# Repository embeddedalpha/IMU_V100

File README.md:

# Innertial Measurement System

## Version: 1.0.0

## Project Structure

```

    📁 Case
    📁 Firmware
    📁 Marketing and Documentation
    📁 Media
    📁 PCB
    📁 Software
    📁 Simulations
    📁 Wires and Cables
    📄 README.md

```

## Architecture

### [Architecture's PDF](PCB/PDFs/IMU_V100.pdf)

### [EW0201DW](Drawings/EW0201DW.pdf)

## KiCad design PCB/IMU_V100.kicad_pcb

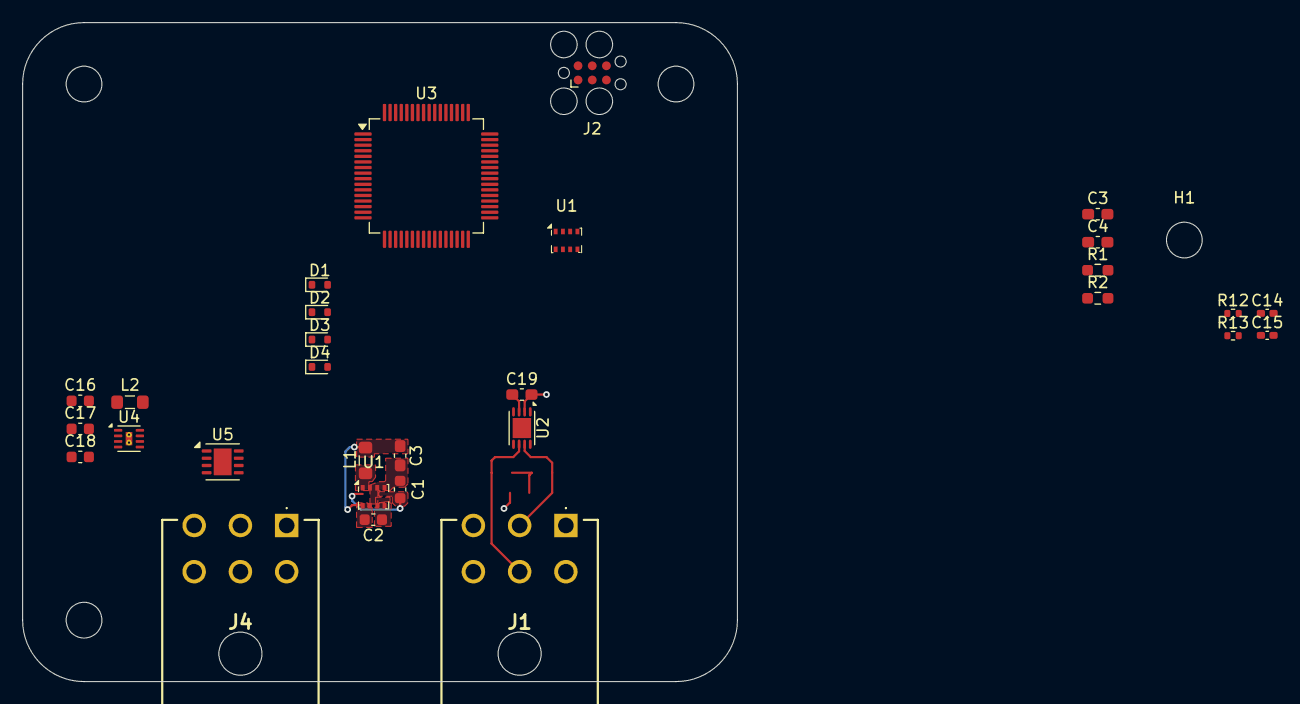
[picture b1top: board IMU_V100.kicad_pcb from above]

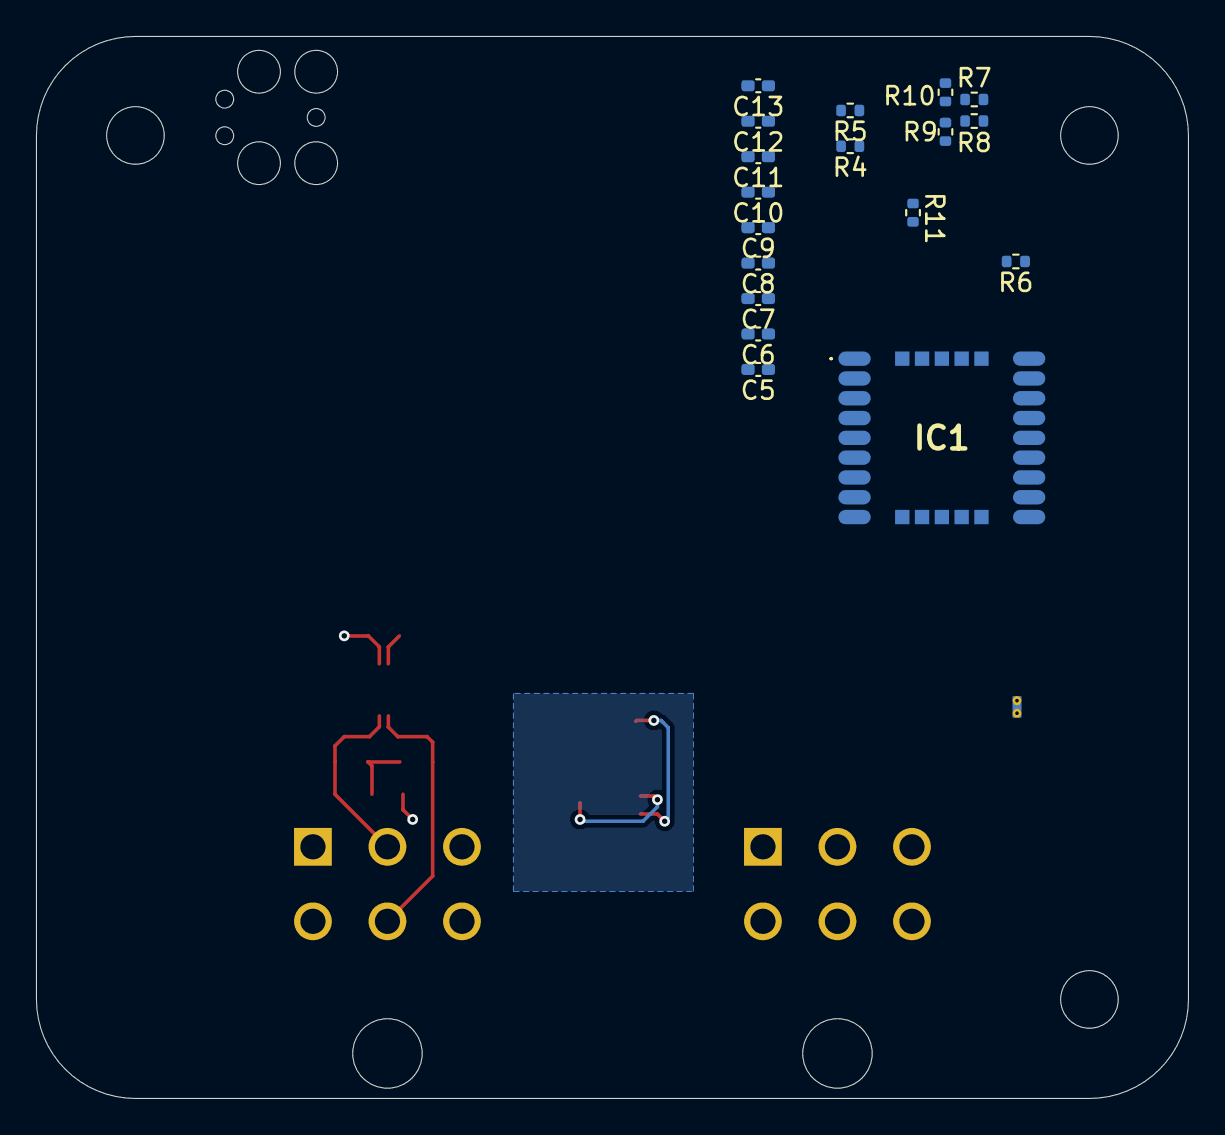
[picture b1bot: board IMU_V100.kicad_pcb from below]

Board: 2 copper layers, 64.0 x 59.0 mm, 52 parts (18 on the bottom side), 25 nets.

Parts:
C1, C16, C18: 4.7uF; C_0603_1608Metric
C2, C17: 560nF; C_0603_1608Metric
C3, C3#2, C19: 0.1uF; C_0603_1608Metric_Pad1.08x0.95mm_HandSolder
C4: 4700pF; C_0603_1608Metric_Pad1.08x0.95mm_HandSolder
C5, C7, C10: 10uF; C_0402_1005Metric_Pad0.74x0.62mm_HandSolder
C6, C8, C13: 100nF; C_0402_1005Metric_Pad0.74x0.62mm_HandSolder
C9, C12, C15: C; C_0402_1005Metric_Pad0.74x0.62mm_HandSolder
C11, C14: 33pF; C_0402_1005Metric_Pad0.74x0.62mm_HandSolder
D1, D2, D3, D4: ESD5Zxx; D_SOD-523
H1, H2, H3: MountingHole; MountingHole_3.2mm_M3_DIN965
Hd1: MountingHole; MountingHole_3.2mm_M3_DIN965
IC1: LC76GABMD
J1, J4: 1-770969-0; 17709690
J2: Conn_ARM_SWD_TagConnect_TC2030; Tag-Connect_TC2030-IDC-FP_2x03_P1.27mm_Vertical
L1, L2: 1uH; L_0805_2012Metric_Pad1.05x1.20mm_HandSolder
R1, R2: 60R; R_0603_1608Metric_Pad0.98x0.95mm_HandSolder
R4, R5, R6, R7: R; R_0402_1005Metric
R8, R9, R10: 0R; R_0402_1005Metric
R11, R12: 2.2K; R_0402_1005Metric
R13: 10K; R_0402_1005Metric
U1, U1#2: BMP280; Bosch_LGA-8_2x2.5mm_P0.65mm_ClockwisePinNumbering
U2: MCP2557FD-xMNY; TDFN-8-1EP_3x2mm_P0.5mm_EP1.80x1.65mm
U3: STM32G0B1RCTx; LQFP-64_10x10mm_P0.5mm
U4: MIC23050-SYML; Micrel_MLF-8-1EP_2x2mm_P0.5mm_EP0.6x1.2mm_ThermalVias
U5: THVD1450DR; VSON-8-1EP_3x3mm_P0.65mm_EP1.6x2.4mm

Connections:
+3V3: C3.2 (-), C3#2.2 (-), C5.1 (+), C6.1 (+), C7.1 (+), C8.1 (+), C11.1 (+), C17.1, C18.1, C19.2 (-), D1.1 (K), IC1.8 (VCC), J2.1 (VCC), L2.2, R11.1 (+), R12.1 (+), R13.1 (+), U1.6 (VDDIO), U1.8 (VDD), U1#2.6 (VDDIO), U1#2.8 (VDD), U2.3 (VDD), U4.4 (SNS), U5.8 (VCC)
/3V3: C2.1, L1.2
/Project_Architecture/Barometer/CLK_BMP280: U1.4 (SCK), U1#2.4 (SCK)
/Project_Architecture/Barometer/MISO_BMP280: U1.3 (SDI), U1#2.3 (SDI)
/Project_Architecture/Barometer/MOSI_BMP280: U1.5 (SDO), U1#2.5 (SDO)
/Project_Architecture/Barometer/nCSS_BMP280: U1.2 (CSB), U1#2.2 (CSB)
/Project_Architecture/CAN_FD/VIN: C16.1, J1.1, J4.1, U4.2 (EN), U4.7 (VIN)
/Project_Architecture/GPS/I2C_SCL_GNSS: R10.2 (-), R11.2 (-)
/Project_Architecture/GPS/I2C_SDA_GNSS: R9.2 (-), R12.2 (-)
/Project_Architecture/Power/CFF: C17.2, U4.5 (CFF)
GND: C1.2, C3.1 (+), C3#2.1 (+), C4.1 (+), C5.2 (-), C6.2 (-), C7.2 (-), C8.2 (-), C10.2 (-), C11.2 (-), C12.1 (+), C13.2 (-), C14.2 (-), C15.1 (+), C16.2, C18.2, C19.1 (+), D1.2 (A), D2.2 (A), D3.2 (A), D4.2 (A), IC1.1 (GND_1), IC1.10 (GND_2), IC1.12 (GND_3), IC1.28 (GND_4), J1.4, J2.5 (GND), J4.4, U1.1 (GND), U1.7 (GND), U1#2.1 (GND), U1#2.7 (GND), U2.2 (VSS), U2.9 (VSS), U4.6 (AGND), U4.8 (PGND), U4.9 (EP_GND)
unnamed: C10.1 (+), C13.1 (+), C14.1 (+), IC1.6 (V_BCKP)
unnamed: C4.2 (-), R1.1 (+), R2.2 (-)
unnamed: C9.2 (-), C12.2 (-), R6.1 (+)
unnamed: C15.2 (-), IC1.11 (RF_IN), R6.2 (-)
unnamed: IC1.17 (I2C_SCL), R10.1 (+)
unnamed: IC1.16 (I2C_SDA), R9.1 (+)
unnamed: IC1.24 (RESERVED_5), R13.2 (-)
unnamed: IC1.9 (RESET_N), R8.2 (-)
unnamed: IC1.14 (VDD_RF), R5.2 (-), R7.2 (-)
unnamed: R5.1 (+), R7.1 (+)
unnamed: J1.2, R1.2 (-), U2.7 (CANH)
unnamed: J1.5, R2.1 (+), U2.6 (CANL)
unnamed: U5.2 (~RE), U5.3 (DE)
unnamed: L2.1, U4.1 (SW)

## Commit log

2025-01-05 Added Foundation of firmware
2025-01-06 Updated firmware
2025-02-03 First Commit of PCB files
2025-02-04 Updated Firmware. Added BMP280
2025-02-06 Updated PCB
2025-02-10 Updated PCB. Added Debug section and rectifed RS485
2025-02-11 Updated PCB.
2025-02-12 Updated Project
2025-02-16 Updated RS485 Cable
2025-02-20 Updated FIRMWARE. CAN Driver Added
2025-02-21 EW0201DW Updated
2025-02-21 Updated Marketing Material
2025-03-06 Updated repo
2025-03-07 Updated Modbus Driver
2025-03-09 Updated Modbus Driver and Modbus Comms
2025-03-14 Added Command List
2025-03-15 Added Simulation Folder
2025-03-16 Added Simulation
2025-03-17 Updated Pcb
2025-03-22 Revamped DMA Driver to accomodate Callbacks to increase modularity and reduce code size.
2025-03-22 corrected timer configuration instance
2025-03-22 Added dump.txt for code dumping
2025-03-22 Firmware Directory Update
2025-03-23 Simulations added
2025-03-23 Finalized power section schematic
2025-03-23 Added Simulations
2025-03-26 Updated USART.c to remove errors.
2025-04-19 Updated Firmware- I2C Driver Updated
2025-04-21 Updated Firmware - Added AHRS
